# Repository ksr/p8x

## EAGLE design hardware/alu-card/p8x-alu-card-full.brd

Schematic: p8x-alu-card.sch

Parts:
CD1, CD2, CD3, CD4, CD5, CD6, CD7, CD8, CD9, CD10, CD11, CD12, CD13, CD14, CD15, CD16, CD17, CD18, CD19, CD20, CD21, CD22, CD23, CD24, CD25, CD26, CD27, CD28, CD29, CD30, CD31, CD32, CD33, CD34, CD35: 100nF; C_DISC1
J1: MABC96R
LED3, LED4: GRN; LED5
LED5: YEL; LED5
R4, R5: 1K; R_AXIAL
RP1: 1K; R_AXIAL
U1, U3, U5, U7: 74HCT377; DIP20
U2, U4, U6, U8, U16, U23: 74HCT244; DIP20
U9, U10: 74HCT181; DIP24W
U11: 74HCT182; DIP16
U12, U13, U14, U15, U22, U28, U29, U30, U32, U33: 74HCT157; DIP16
U17: FLAGS; DIP16
U18, U27: 74HCT260; DIP14
U19, U31, U35: 74HCT08; DIP14
U20, U21: 74HCT138; DIP16
U24: 74HCT32; DIP14
U25: 74HCT00; DIP14
U26: 74HCT74; DIP14
U34: 74HCT86; DIP14

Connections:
-CCLR: U26.1 (!1CLR), U31.8 (3Y)
-CLRCb: U25.11 (4Y), U31.10 (3B)
-DOEA: U2.1 (!G1), U2.19 (!G2), U20.14 (Y1)
-DOEALU: U16.1 (!G1), U16.19 (!G2), U19.9 (3A), U19.10 (3B), U20.10 (Y5)
-DOEB: U4.1 (!G1), U4.19 (!G2), U20.13 (Y2)
-DOEFLG: U20.9 (Y6), U23.1 (!G1)
-DOET: U6.1 (!G1), U6.19 (!G2), U20.12 (Y3)
-DOET2: U8.1 (!G1), U8.19 (!G2), U20.11 (Y4)
-LDA: U1.1 (!E), U21.14 (Y1)
-LDB: U3.1 (!E), U21.13 (Y2)
-LDT: U5.1 (!E), U21.12 (Y3)
-LDT2: U7.1 (!E), U21.11 (Y4)
-RES: J1.A11, U17.1 (!CLR), U31.9 (3A)
-SETCb: U25.3 (1Y), U26.4 (!1PRE)
ALUK: LED4.1 (K), U19.8 (3Y)
ALUM: J1.C23, U9.8 (M), U10.8 (M)
ALUS0: J1.C19, U9.6 (S0), U10.6 (S0)
ALUS1: J1.C20, U9.5 (S1), U10.5 (S1)
ALUS2: J1.C21, U9.4 (S2), U10.4 (S2), U34.9 (3A)
ALUS3: J1.C22, U9.3 (S3), U10.3 (S3)
AQ0: U1.2 (Q1), U2.2 (A1), U9.2 (A0)
AQ1: U1.5 (Q2), U2.4 (A2), U9.23 (A1)
AQ2: U1.6 (Q3), U2.6 (A3), U9.21 (A2)
AQ3: U1.9 (Q4), U2.8 (A4), U9.19 (A3)
AQ4: U1.12 (Q5), U2.11 (A5), U10.2 (A0)
AQ5: U1.15 (Q6), U2.13 (A6), U10.23 (A1)
AQ6: U1.16 (Q7), U2.15 (A7), U10.21 (A2)
AQ7: U1.19 (Q8), U2.17 (A8), U10.19 (A3), U34.1 (1A), U34.4 (2A)
BMX0: U9.1 (B0), U32.4 (Y1)
BMX1: U9.22 (B1), U32.7 (Y2)
BMX2: U9.20 (B2), U32.9 (Y3)
BMX3: U9.18 (B3), U32.12 (Y4)
BMX4: U10.1 (B0), U33.4 (Y1)
BMX5: U10.22 (B1), U33.7 (Y2)
BMX6: U10.20 (B2), U33.9 (Y3)
BMX7: U10.18 (B3), U33.12 (Y4), U34.5 (2B)
BQ0: U3.2 (Q1), U4.2 (A1), U32.2 (A1)
BQ1: U3.5 (Q2), U4.4 (A2), U32.5 (A2)
BQ2: U3.6 (Q3), U4.6 (A3), U32.11 (A3)
BQ3: U3.9 (Q4), U4.8 (A4), U32.14 (A4)
BQ4: U3.12 (Q5), U4.11 (A5), U33.2 (A1)
BQ5: U3.15 (Q6), U4.13 (A6), U33.5 (A2)
BQ6: U3.16 (Q7), U4.15 (A7), U33.11 (A3)
BQ7: U3.19 (Q8), U4.17 (A8), U33.14 (A4)
BSEL: J1.B28, U32.1 (S), U33.1 (S)
CFLG: U10.16 (CN4), U25.4 (2A), U25.5 (2B)
CFLGI: U25.6 (2Y), U29.2 (A1)
CG0: U9.17 (!G), U11.3 (!G0)
CG1: U10.17 (!G), U11.1 (!G1)
CIN: J1.C24, U9.7 (CN), U11.13 (CN), U30.2 (A1)
CLK: J1.A24, U1.11 (CLK), U3.11 (CLK), U5.11 (CLK), U7.11 (CLK), U31.1 (1A), U31.5 (2B)
CLKFC: U26.3 (1CLK), U31.3 (1Y)
CLKFZN: U17.9 (CLK), U31.6 (2Y)
CLRC: J1.B27, U25.12 (4A), U25.13 (4B)
CNX: U10.7 (CN), U11.12 (CNX)
CP0: U9.15 (!P), U11.4 (!P0)
CP1: U10.15 (!P), U11.2 (!P1)
D0: J1.A3, U1.3 (D1), U2.18 (Y1), U3.3 (D1), U4.18 (Y1), U5.3 (D1), U6.18 (Y1), U7.3 (D1), U8.18 (Y1), U16.18 (Y1), U23.18 (Y1), U27.1 (A1)
D1: J1.A4, U1.4 (D2), U2.16 (Y2), U3.4 (D2), U4.16 (Y2), U5.4 (D2), U6.16 (Y2), U7.4 (D2), U8.16 (Y2), U16.16 (Y2), U23.16 (Y2), U27.2 (B1)
D2: J1.A5, U1.7 (D3), U2.14 (Y3), U3.7 (D3), U4.14 (Y3), U5.7 (D3), U6.14 (Y3), U7.7 (D3), U8.14 (Y3), U16.14 (Y3), U23.14 (Y3), U27.11 (C1)
D3: J1.A6, U1.8 (D4), U2.12 (Y4), U3.8 (D4), U4.12 (Y4), U5.8 (D4), U6.12 (Y4), U7.8 (D4), U8.12 (Y4), U16.12 (Y4), U23.12 (Y4), U27.12 (D1)
D4: J1.A7, U1.13 (D5), U2.9 (Y5), U3.13 (D5), U4.9 (Y5), U5.13 (D5), U6.9 (Y5), U7.13 (D5), U8.9 (Y5), U16.9 (Y5), U27.13 (E1)
D5: J1.A8, U1.14 (D6), U2.7 (Y6), U3.14 (D6), U4.7 (Y6), U5.14 (D6), U6.7 (Y6), U7.14 (D6), U8.7 (Y6), U16.7 (Y6), U27.3 (A2)
D6: J1.A9, U1.17 (D7), U2.5 (Y7), U3.17 (D7), U4.5 (Y7), U5.17 (D7), U6.5 (Y7), U7.17 (D7), U8.5 (Y7), U16.5 (Y7), U27.4 (B2)
D7: J1.A10, U1.18 (D8), U2.3 (Y8), U3.18 (D8), U4.3 (Y8), U5.18 (D8), U6.3 (Y8), U7.18 (D8), U8.3 (Y8), U16.3 (Y8), U22.6 (B2), U27.5 (C2)
DLD0: J1.A16, U21.1 (A)
DLD1: J1.A17, U21.2 (B)
DLD2: J1.A18, U21.3 (C)
DLD3: J1.A19, U21.4 (!G2A)
DOE0: J1.A12, U20.1 (A)
DOE1: J1.A13, U20.2 (B)
DOE2: J1.A14, U20.3 (C)
DOE3: J1.A15, U20.4 (!G2A)
F0: U9.9 (F0), U12.2 (A1), U12.6 (B2), U28.2 (A1)
F1: U9.10 (F1), U12.5 (A2), U12.10 (B3)
F2: U9.11 (F2), U12.11 (A3), U12.13 (B4)
F3: U9.13 (F3), U12.14 (A4), U13.3 (B1)
F4: U10.9 (F0), U13.2 (A1), U13.6 (B2)
F5: U10.10 (F1), U13.5 (A2), U13.10 (B3)
F6: U10.11 (F2), U13.11 (A3), U13.13 (B4)
F7: U10.13 (F3), U13.14 (A4), U28.3 (B1), U34.2 (1B)
FC: J1.A27, U23.9 (Y5)
FENZN: U24.3 (1Y), U31.4 (2A)
FN: J1.A29, U23.5 (Y7)
FQC: U23.2 (A1), U23.11 (A5), U26.5 (1Q), U30.3 (B1)
FQN: U17.7 (Q2), U23.6 (A3), U23.15 (A7)
FQV: U17.10 (Q3), U23.8 (A4), U23.17 (A8)
FQZ: U17.2 (Q1), U23.4 (A2), U23.13 (A6)
FV: J1.A30, U23.3 (Y8)
FZ: J1.A28, U23.7 (Y6)
G0: U12.4 (Y1), U14.2 (A1)
G1: U12.7 (Y2), U14.3 (B1), U14.5 (A2)
G2: U12.9 (Y3), U14.6 (B2), U14.11 (A3)
G3: U12.12 (Y4), U14.10 (B3), U14.14 (A4)
G4: U13.4 (Y1), U14.13 (B4), U15.2 (A1)
G5: U13.7 (Y2), U15.3 (B1), U15.5 (A2)
G6: U13.9 (Y3), U15.6 (B2), U15.11 (A3)
G7: U13.12 (Y4), U15.10 (B3), U15.14 (A4)
GND: CD1.2, CD2.2, CD3.2, CD4.2, CD5.2, CD6.2, CD7.2, CD8.2, CD9.2, CD10.2, CD11.2, CD12.2, CD13.2, CD14.2, CD15.2, CD16.2, CD17.2, CD18.2, CD19.2, CD20.2, CD21.2, CD22.2, CD23.2, CD24.2, CD25.2, CD26.2, CD27.2, CD28.2, CD29.2, CD30.2, CD31.2, CD32.2, CD33.2, CD34.2, CD35.2, J1.A31, J1.A32, J1.B3, J1.B5, J1.B7, J1.B9, J1.B11, J1.B13, J1.B15, J1.B17, J1.B19, J1.B21, J1.B23, J1.B25, J1.B31, J1.B32, J1.C31, J1.C32, LED3.1 (K), U1.10 (GND), U2.10 (GND), U3.10 (GND), U4.10 (GND), U5.10 (GND), U6.10 (GND), U7.10 (GND), U8.10 (GND), U9.12 (GND), U10.12 (GND), U11.8 (GND), U12.8 (GND), U12.15 (!G), U13.8 (GND), U13.15 (!G), U14.8 (GND), U14.15 (!G), U15.8 (GND), U15.15 (!G), U16.10 (GND), U17.8 (GND), U18.7 (GND), U18.9 (D2), U18.10 (E2), U19.7 (GND), U19.12 (4A), U19.13 (4B), U20.5 (!G2B), U20.8 (GND), U21.5 (!G2B), U21.8 (GND), U22.8 (GND), U22.15 (!G), U23.10 (GND), U23.19 (!G2), U24.7 (GND), U24.9 (3A), U24.10 (3B), U24.12 (4A), U24.13 (4B), U25.7 (GND), U26.7 (GND), U26.11 (2CLK), U26.12 (2D), U27.7 (GND), U27.9 (D2), U27.10 (E2), U28.8 (GND), U28.15 (!G), U29.8 (GND), U29.15 (!G), U30.8 (GND), U30.15 (!G), U31.7 (GND)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
LDF: J1.A26, U24.1 (1A), U25.9 (3A), U25.10 (3B), U31.2 (1B)
LDFK: LED5.1 (K), U25.8 (3Y)
LDZN: J1.C28, U22.1 (S), U24.2 (1B)
LEDAL: LED4.2 (A), R4.2
LEDLF: LED5.2 (A), R5.2
LEDP: LED3.2 (A), RP1.2
NC: U26.2 (1D), U29.4 (Y1)
NS2: U34.8 (3Y), U34.13 (4B)
NSRC: U17.5 (D2), U22.7 (Y2)
R0: U14.4 (Y1), U16.2 (A1), U18.1 (A1)
R1: U14.7 (Y2), U16.4 (A2), U18.2 (B1)
R2: U14.9 (Y3), U16.6 (A3), U18.11 (C1)
R3: U14.12 (Y4), U16.8 (A4), U18.12 (D1)
R4: U15.4 (Y1), U16.11 (A5), U18.13 (E1)
R5: U15.7 (Y2), U16.13 (A6), U18.3 (A2)
R6: U15.9 (Y3), U16.15 (A7), U18.4 (B2)
R7: U15.12 (Y4), U16.17 (A8), U18.5 (C2), U22.5 (A2)
SETC: J1.C30, U25.1 (1A), U25.2 (1B)
SH0: J1.C25, U12.1 (S), U13.1 (S), U24.4 (2A), U28.1 (S)
SH1: J1.C26, U14.1 (S), U15.1 (S), U24.5 (2B)
SHANY: U24.6 (2Y), U29.1 (S)
SHCIN: J1.C29, U30.1 (S)
SHIN: U12.3 (B1), U15.13 (B4), U30.4 (Y1)
SHOUT: U28.4 (Y1), U29.3 (B1)
T2Q0: U7.2 (Q1), U8.2 (A1)
T2Q1: U7.5 (Q2), U8.4 (A2)
T2Q2: U7.6 (Q3), U8.6 (A3)
T2Q3: U7.9 (Q4), U8.8 (A4)
T2Q4: U7.12 (Q5), U8.11 (A5)
T2Q5: U7.15 (Q6), U8.13 (A6)
T2Q6: U7.16 (Q7), U8.15 (A7)
T2Q7: U7.19 (Q8), U8.17 (A8)
TQ0: U5.2 (Q1), U6.2 (A1), U32.3 (B1)
TQ1: U5.5 (Q2), U6.4 (A2), U32.6 (B2)
TQ2: U5.6 (Q3), U6.6 (A3), U32.10 (B3)
TQ3: U5.9 (Q4), U6.8 (A4), U32.13 (B4)
TQ4: U5.12 (Q5), U6.11 (A5), U33.3 (B1)
TQ5: U5.15 (Q6), U6.13 (A6), U33.6 (B2)
TQ6: U5.16 (Q7), U6.15 (A7), U33.10 (B3)
TQ7: U5.19 (Q8), U6.17 (A8), U33.13 (B4)
VCC: CD1.1, CD2.1, CD3.1, CD4.1, CD5.1, CD6.1, CD7.1, CD8.1, CD9.1, CD10.1, CD11.1, CD12.1, CD13.1, CD14.1, CD15.1, CD16.1, CD17.1, CD18.1, CD19.1, CD20.1, CD21.1, CD22.1, CD23.1, CD24.1, CD25.1, CD26.1, CD27.1, CD28.1, CD29.1, CD30.1, CD31.1, CD32.1, CD33.1, CD34.1, CD35.1, J1.A1, J1.A2, J1.B1, J1.B2, J1.C1, J1.C2, R4.1, R5.1, RP1.1, U1.20 (VCC), U2.20 (VCC), U3.20 (VCC), U4.20 (VCC), U5.20 (VCC), U6.20 (VCC), U7.20 (VCC), U8.20 (VCC), U9.24 (VCC), U10.24 (VCC), U11.5 (!G3), U11.6 (!P3), U11.14 (!P2), U11.15 (!G2), U11.16 (VCC), U12.16 (VCC), U13.16 (VCC), U14.16 (VCC), U15.16 (VCC), U16.20 (VCC), U17.16 (VCC), U18.14 (VCC), U19.14 (VCC), U20.6 (G1), U20.16 (VCC), U21.6 (G1), U21.16 (VCC), U22.16 (VCC), U23.20 (VCC), U24.14 (VCC), U25.14 (VCC), U26.10 (!2PRE), U26.13 (!2CLR), U26.14 (VCC), U27.14 (VCC), U28.16 (VCC), U29.16 (VCC), U30.16 (VCC), U31.14 (VCC), U32.16 (VCC), U33.16 (VCC), U34.10 (3B), U34.14 (VCC), U35.14 (VCC)
VSRC: U17.12 (D3), U35.3 (1Y)
VX1: U34.3 (1Y), U35.1 (1A)
VX2: U34.6 (2Y), U34.12 (4A)
VX4: U34.11 (4Y), U35.2 (1B)
ZBH: U19.5 (2B), U27.6 (Y2)
ZBL: U19.4 (2A), U27.8 (Y1)
ZBUS: U19.6 (2Y), U22.3 (B1)
ZFLG: U19.3 (1Y), U22.2 (A1)
ZH: U18.6 (Y2), U19.2 (1B)
ZL: U18.8 (Y1), U19.1 (1A)
ZSRC: U17.4 (D1), U22.4 (Y1)

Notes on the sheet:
P8X ALU CARD REV B (conventional carry, LDZN, SETC/CLRC, carry-coupled shifter)
CLK/FORCE GATES
74HCT08
V XOR
74HCT86
V AND
A REG
74HCT377
A OUT
74HCT244
B REG
B OUT
T REG
T OUT
T2 REG
T2 OUT
ALU LO
74HCT181
ALU HI
CLA
74HCT182
SH1 LO
74HCT157
SH1 HI
SH2 LO
SH2 HI
ALU OUT
Z DET
74HCT260
DOE DEC
74HCT138
DLD DEC
FLAG MUX
FLAG OUT
C FLAG FF
74HCT74
BUS Z-DET
SHIFT-OUT MUX
C-SRC MUX
SHIN MUX

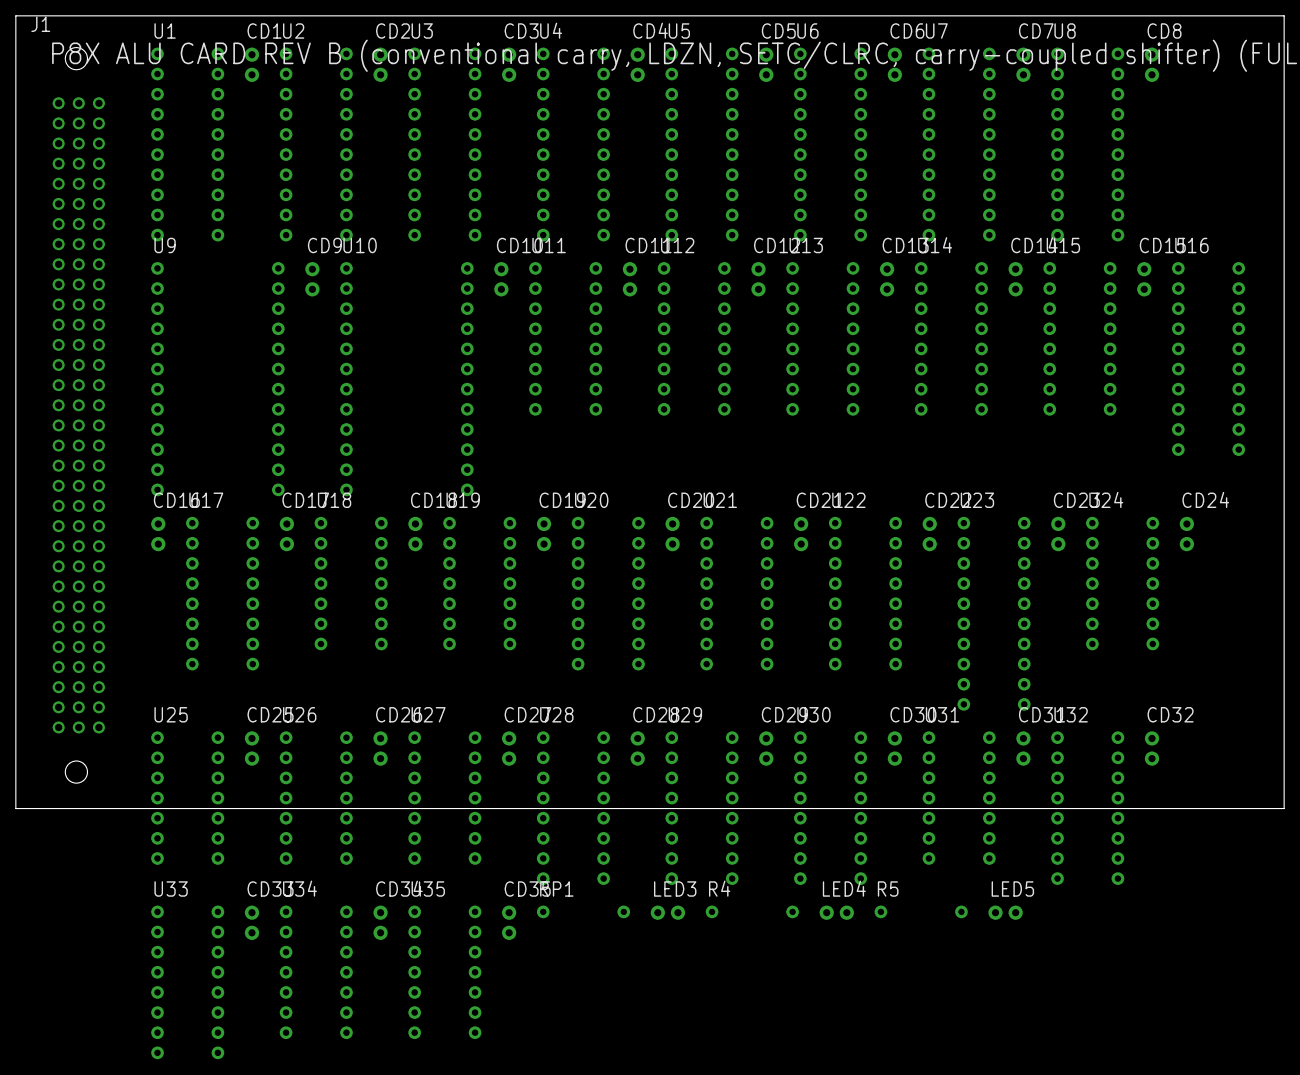
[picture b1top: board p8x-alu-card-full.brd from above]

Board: 4 copper layers, 160.0 x 100.0 mm, 77 parts (0 on the bottom side), 151 nets, no tracks yet.

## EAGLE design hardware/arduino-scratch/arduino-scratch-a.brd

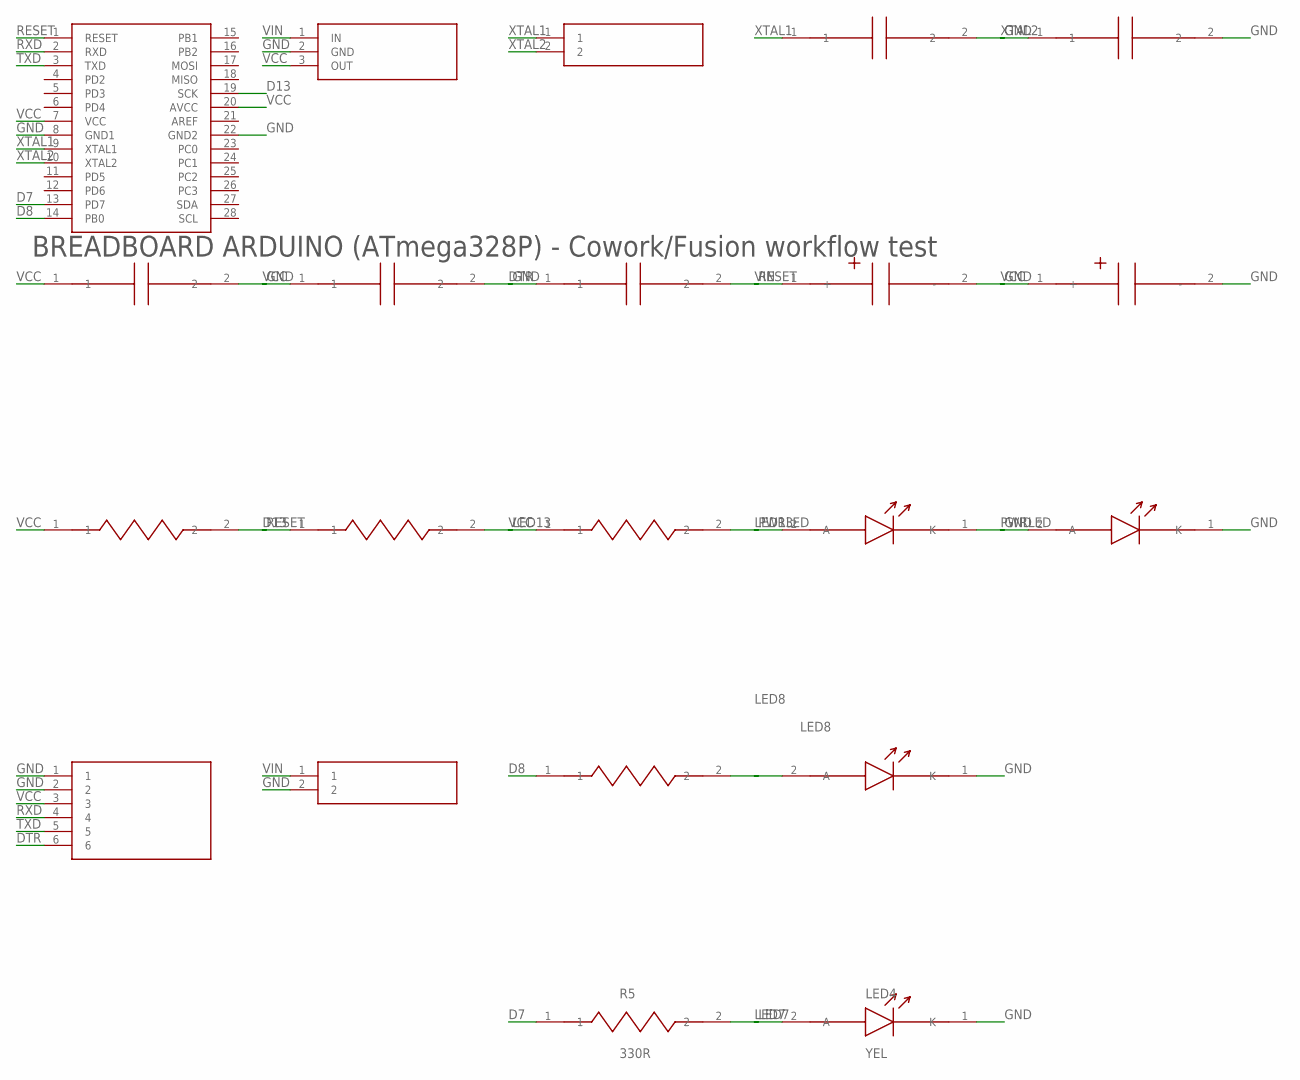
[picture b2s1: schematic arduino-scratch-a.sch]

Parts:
C1, C2: 22P; C_DISC
C3, C4, C5: 100N; C_DISC
C6, C7: 10U; CP_RADIAL
J1: FTDI; HDR6
J2: 7-12V DC; HDR2
LED1, LED3, LED4: YEL; LED5
LED2: GRN; LED5
R1: 10K; R_AXIAL
R2, R4, R5: 330R; R_AXIAL
R3: 1K; R_AXIAL
U1: ATMEGA328P-PU; DIP28N
U2: 7805; TO220
Y1: 16MHZ; HC49

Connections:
D7: R5.1, U1.13 (PD7)
D8: R4.1, U1.14 (PB0)
D13: R2.1, U1.19 (SCK)
DTR: C5.1, J1.6
GND: C1.2, C2.2, C3.2, C4.2, C6.2 (-), C7.2 (-), J1.1, J1.2, J2.2, LED1.1 (K), LED2.1 (K), LED3.1 (K), LED4.1 (K), U1.8 (GND1), U1.22 (GND2), U2.2 (GND)
LED7: LED4.2 (A), R5.2
LED8: LED3.2 (A), R4.2
LED13: LED1.2 (A), R2.2
PWRLED: LED2.2 (A), R3.2
RESET: C5.2, R1.2, U1.1 (RESET)
RXD: J1.4, U1.2 (RXD)
TXD: J1.5, U1.3 (TXD)
VCC: C3.1, C4.1, C7.1 (+), J1.3, R1.1, R3.1, U1.7 (VCC), U1.20 (AVCC), U2.3 (OUT)
VIN: C6.1 (+), J2.1, U2.1 (IN)
XTAL1: C1.1, U1.9 (XTAL1), Y1.1
XTAL2: C2.1, U1.10 (XTAL2), Y1.2

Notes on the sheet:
BREADBOARD ARDUINO (ATmega328P) - Cowork/Fusion workflow test

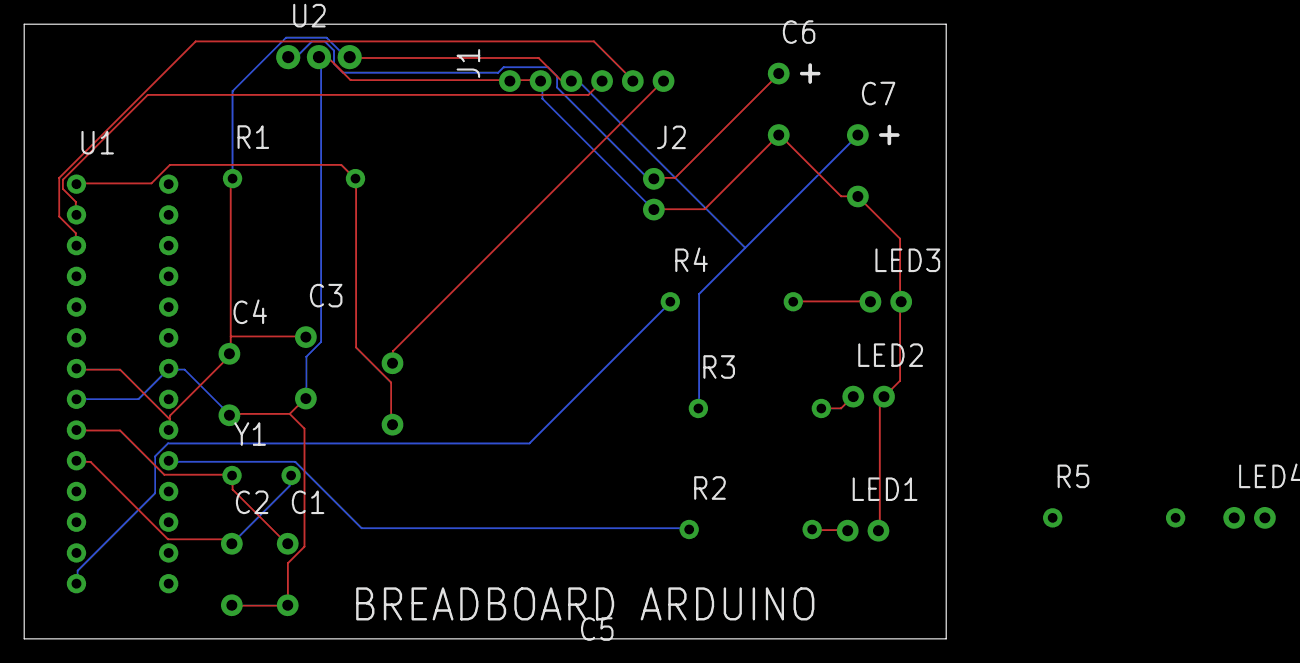
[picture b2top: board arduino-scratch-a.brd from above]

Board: 4 copper layers, 76.2 x 50.8 mm, 21 parts (0 on the bottom side), 16 nets.

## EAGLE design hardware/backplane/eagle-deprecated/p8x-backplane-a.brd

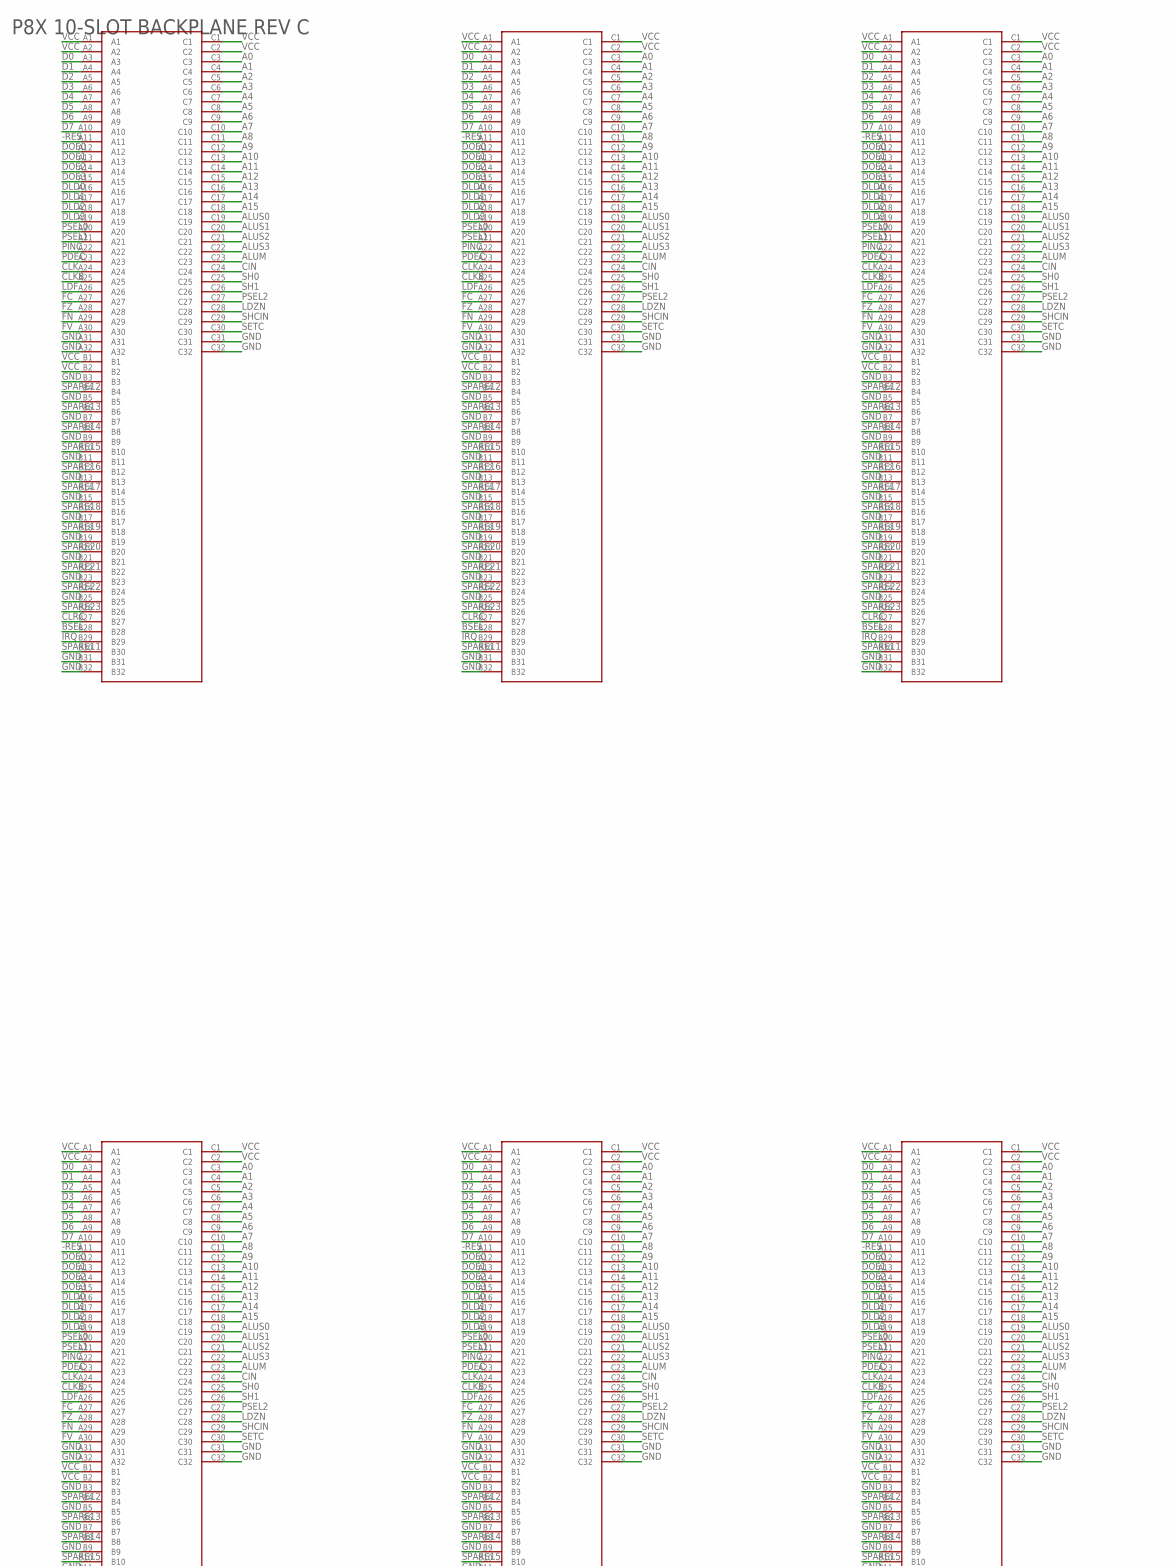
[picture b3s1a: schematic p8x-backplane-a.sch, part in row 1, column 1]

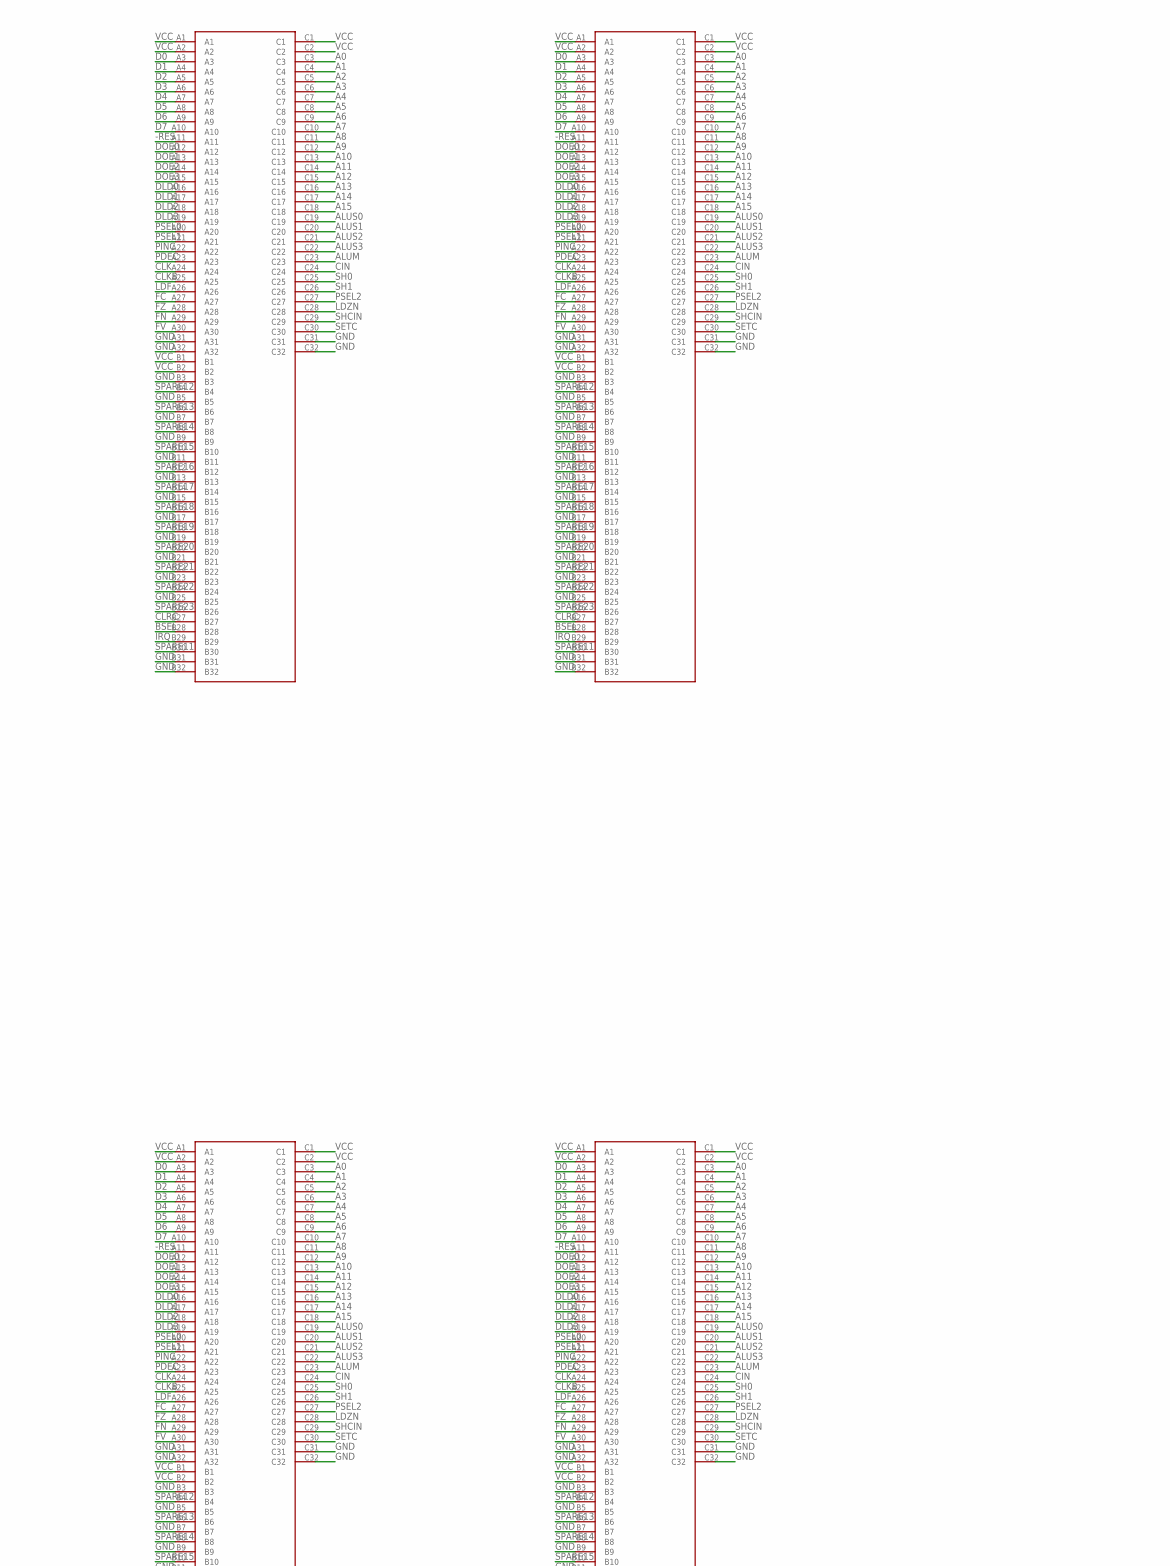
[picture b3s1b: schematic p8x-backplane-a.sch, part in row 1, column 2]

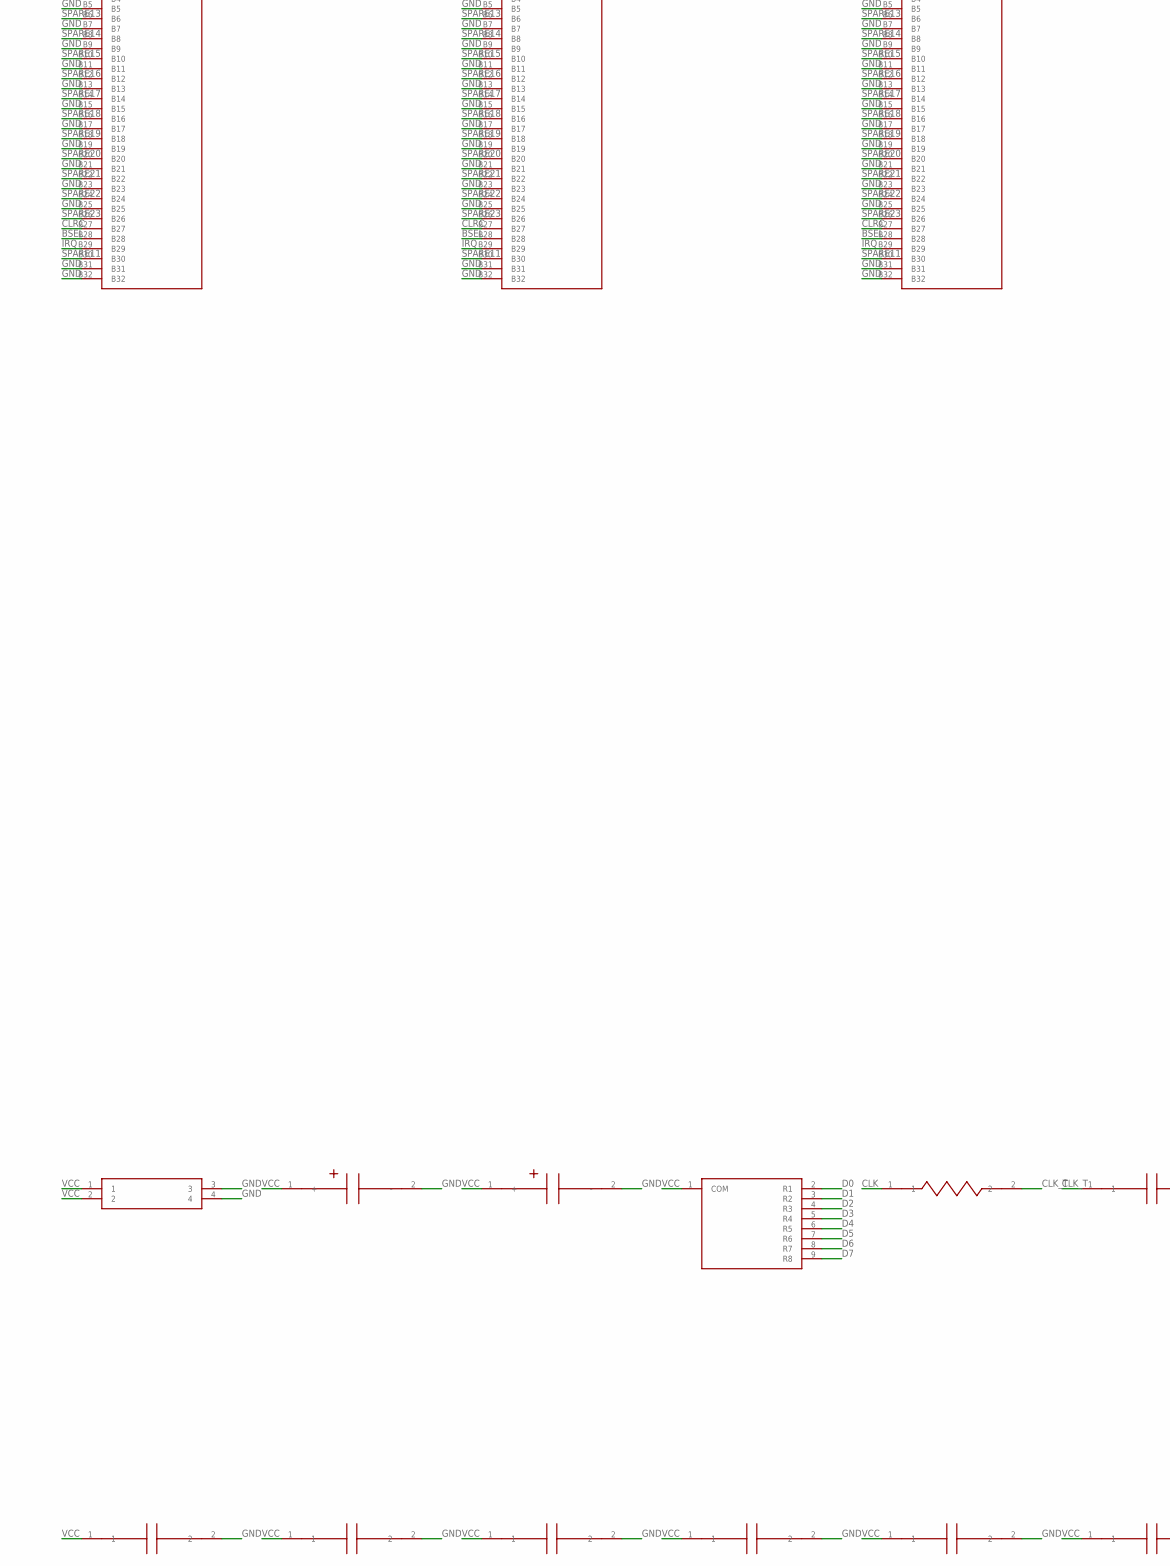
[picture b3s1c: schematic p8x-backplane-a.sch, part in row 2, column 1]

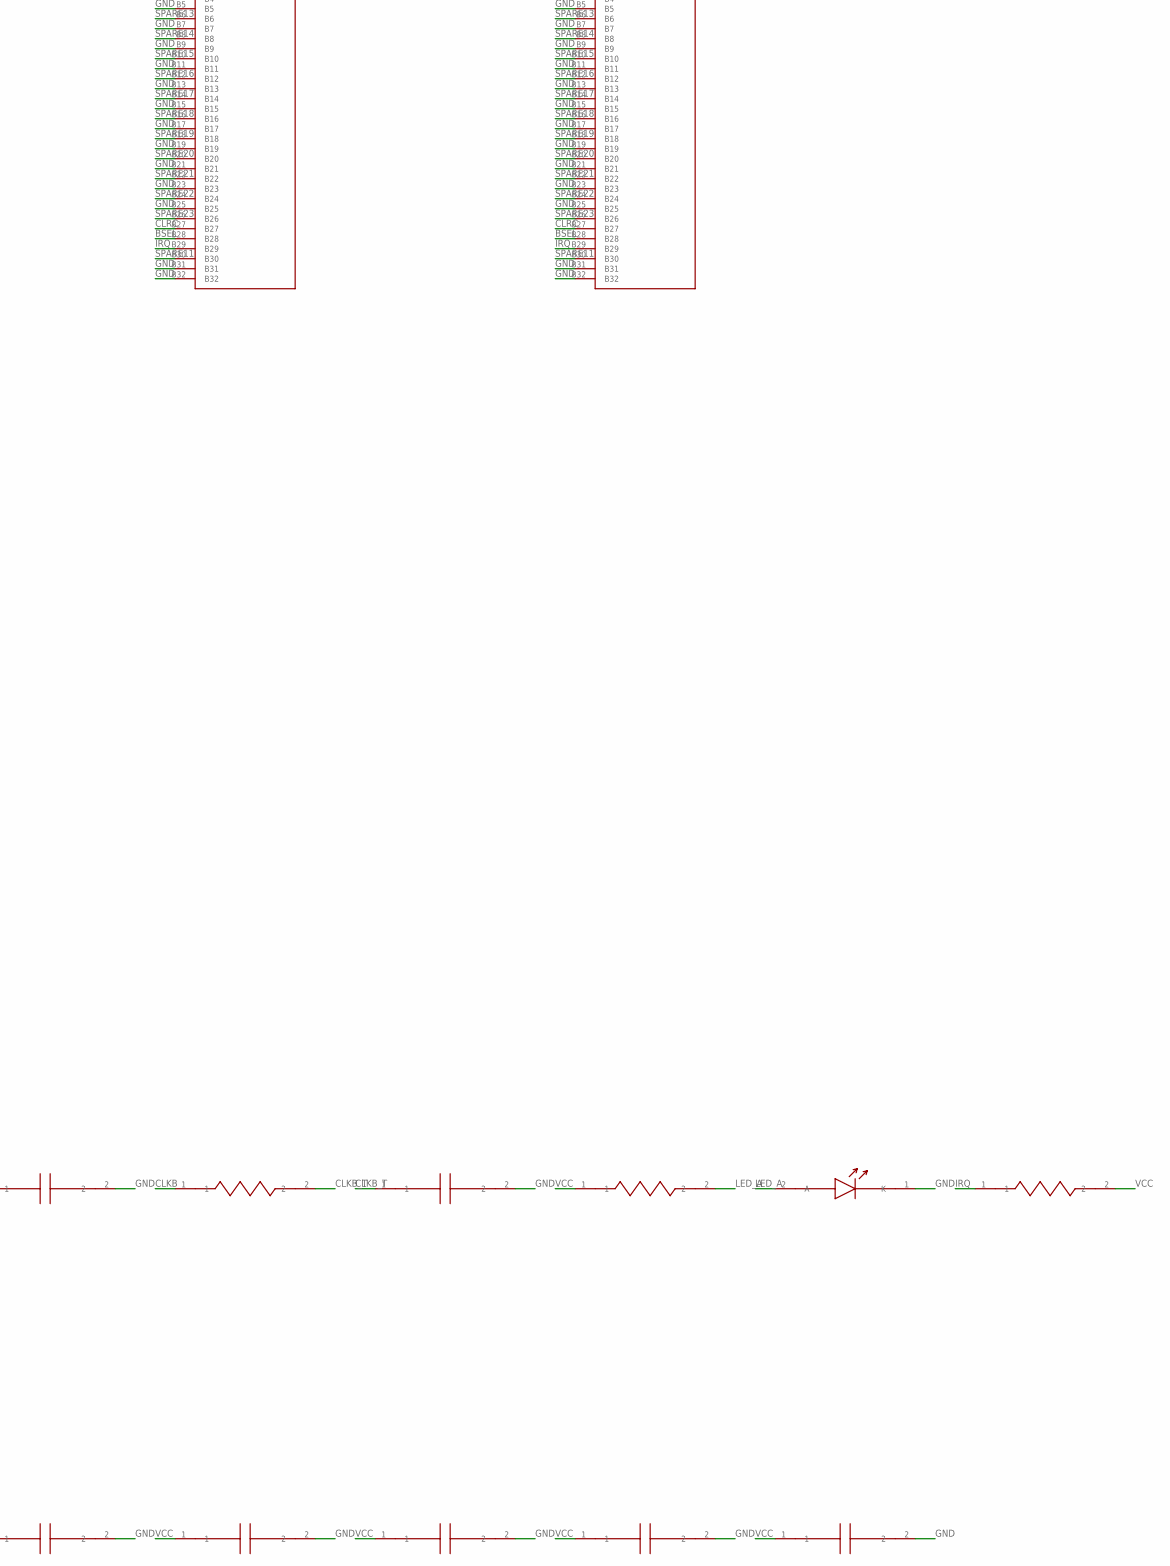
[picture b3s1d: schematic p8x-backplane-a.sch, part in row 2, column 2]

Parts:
C1, C2, C3, C4, C5, C6, C7, C8, C9, C10: 100nF; C_DISC1
C11, C12: 470uF; CP_RADIAL
C13, C14: 150pF; C_DISC
J1: SLOT1; FABC96S
J2: SLOT2; FABC96S
J3: SLOT3; FABC96S
J4: SLOT4; FABC96S
J5: SLOT5; FABC96S
J6: SLOT6; FABC96S
J7: SLOT7; FABC96S
J8: SLOT8; FABC96S
J9: SLOT9; FABC96S
J10: SLOT10; FABC96S
J11: PWR-5V; TB4
LED1: PWR; LED5
R1: 1K; R_AXIAL
R2, R3: 100R; R_AXIAL
R4: 10K; R_AXIAL
RN1: 8X10K; SIP9

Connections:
-RES: J1.A11, J2.A11, J3.A11, J4.A11, J5.A11, J6.A11, J7.A11, J8.A11, J9.A11, J10.A11
A0: J1.C3, J2.C3, J3.C3, J4.C3, J5.C3, J6.C3, J7.C3, J8.C3, J9.C3, J10.C3
A1: J1.C4, J2.C4, J3.C4, J4.C4, J5.C4, J6.C4, J7.C4, J8.C4, J9.C4, J10.C4
A2: J1.C5, J2.C5, J3.C5, J4.C5, J5.C5, J6.C5, J7.C5, J8.C5, J9.C5, J10.C5
A3: J1.C6, J2.C6, J3.C6, J4.C6, J5.C6, J6.C6, J7.C6, J8.C6, J9.C6, J10.C6
A4: J1.C7, J2.C7, J3.C7, J4.C7, J5.C7, J6.C7, J7.C7, J8.C7, J9.C7, J10.C7
A5: J1.C8, J2.C8, J3.C8, J4.C8, J5.C8, J6.C8, J7.C8, J8.C8, J9.C8, J10.C8
A6: J1.C9, J2.C9, J3.C9, J4.C9, J5.C9, J6.C9, J7.C9, J8.C9, J9.C9, J10.C9
A7: J1.C10, J2.C10, J3.C10, J4.C10, J5.C10, J6.C10, J7.C10, J8.C10, J9.C10, J10.C10
A8: J1.C11, J2.C11, J3.C11, J4.C11, J5.C11, J6.C11, J7.C11, J8.C11, J9.C11, J10.C11
A9: J1.C12, J2.C12, J3.C12, J4.C12, J5.C12, J6.C12, J7.C12, J8.C12, J9.C12, J10.C12
A10: J1.C13, J2.C13, J3.C13, J4.C13, J5.C13, J6.C13, J7.C13, J8.C13, J9.C13, J10.C13
A11: J1.C14, J2.C14, J3.C14, J4.C14, J5.C14, J6.C14, J7.C14, J8.C14, J9.C14, J10.C14
A12: J1.C15, J2.C15, J3.C15, J4.C15, J5.C15, J6.C15, J7.C15, J8.C15, J9.C15, J10.C15
A13: J1.C16, J2.C16, J3.C16, J4.C16, J5.C16, J6.C16, J7.C16, J8.C16, J9.C16, J10.C16
A14: J1.C17, J2.C17, J3.C17, J4.C17, J5.C17, J6.C17, J7.C17, J8.C17, J9.C17, J10.C17
A15: J1.C18, J2.C18, J3.C18, J4.C18, J5.C18, J6.C18, J7.C18, J8.C18, J9.C18, J10.C18
ALUM: J1.C23, J2.C23, J3.C23, J4.C23, J5.C23, J6.C23, J7.C23, J8.C23, J9.C23, J10.C23
ALUS0: J1.C19, J2.C19, J3.C19, J4.C19, J5.C19, J6.C19, J7.C19, J8.C19, J9.C19, J10.C19
ALUS1: J1.C20, J2.C20, J3.C20, J4.C20, J5.C20, J6.C20, J7.C20, J8.C20, J9.C20, J10.C20
ALUS2: J1.C21, J2.C21, J3.C21, J4.C21, J5.C21, J6.C21, J7.C21, J8.C21, J9.C21, J10.C21
ALUS3: J1.C22, J2.C22, J3.C22, J4.C22, J5.C22, J6.C22, J7.C22, J8.C22, J9.C22, J10.C22
BSEL: J1.B28, J2.B28, J3.B28, J4.B28, J5.B28, J6.B28, J7.B28, J8.B28, J9.B28, J10.B28
CIN: J1.C24, J2.C24, J3.C24, J4.C24, J5.C24, J6.C24, J7.C24, J8.C24, J9.C24, J10.C24
CLK: J1.A24, J2.A24, J3.A24, J4.A24, J5.A24, J6.A24, J7.A24, J8.A24, J9.A24, J10.A24, R2.1
CLKB: J1.A25, J2.A25, J3.A25, J4.A25, J5.A25, J6.A25, J7.A25, J8.A25, J9.A25, J10.A25, R3.1
CLKB_T: C14.1, R3.2
CLK_T: C13.1, R2.2
CLRC: J1.B27, J2.B27, J3.B27, J4.B27, J5.B27, J6.B27, J7.B27, J8.B27, J9.B27, J10.B27
D0: J1.A3, J2.A3, J3.A3, J4.A3, J5.A3, J6.A3, J7.A3, J8.A3, J9.A3, J10.A3, RN1.2 (R1)
D1: J1.A4, J2.A4, J3.A4, J4.A4, J5.A4, J6.A4, J7.A4, J8.A4, J9.A4, J10.A4, RN1.3 (R2)
D2: J1.A5, J2.A5, J3.A5, J4.A5, J5.A5, J6.A5, J7.A5, J8.A5, J9.A5, J10.A5, RN1.4 (R3)
D3: J1.A6, J2.A6, J3.A6, J4.A6, J5.A6, J6.A6, J7.A6, J8.A6, J9.A6, J10.A6, RN1.5 (R4)
D4: J1.A7, J2.A7, J3.A7, J4.A7, J5.A7, J6.A7, J7.A7, J8.A7, J9.A7, J10.A7, RN1.6 (R5)
D5: J1.A8, J2.A8, J3.A8, J4.A8, J5.A8, J6.A8, J7.A8, J8.A8, J9.A8, J10.A8, RN1.7 (R6)
D6: J1.A9, J2.A9, J3.A9, J4.A9, J5.A9, J6.A9, J7.A9, J8.A9, J9.A9, J10.A9, RN1.8 (R7)
D7: J1.A10, J2.A10, J3.A10, J4.A10, J5.A10, J6.A10, J7.A10, J8.A10, J9.A10, J10.A10, RN1.9 (R8)
DLD0: J1.A16, J2.A16, J3.A16, J4.A16, J5.A16, J6.A16, J7.A16, J8.A16, J9.A16, J10.A16
DLD1: J1.A17, J2.A17, J3.A17, J4.A17, J5.A17, J6.A17, J7.A17, J8.A17, J9.A17, J10.A17
DLD2: J1.A18, J2.A18, J3.A18, J4.A18, J5.A18, J6.A18, J7.A18, J8.A18, J9.A18, J10.A18
DLD3: J1.A19, J2.A19, J3.A19, J4.A19, J5.A19, J6.A19, J7.A19, J8.A19, J9.A19, J10.A19
DOE0: J1.A12, J2.A12, J3.A12, J4.A12, J5.A12, J6.A12, J7.A12, J8.A12, J9.A12, J10.A12
DOE1: J1.A13, J2.A13, J3.A13, J4.A13, J5.A13, J6.A13, J7.A13, J8.A13, J9.A13, J10.A13
DOE2: J1.A14, J2.A14, J3.A14, J4.A14, J5.A14, J6.A14, J7.A14, J8.A14, J9.A14, J10.A14
DOE3: J1.A15, J2.A15, J3.A15, J4.A15, J5.A15, J6.A15, J7.A15, J8.A15, J9.A15, J10.A15
FC: J1.A27, J2.A27, J3.A27, J4.A27, J5.A27, J6.A27, J7.A27, J8.A27, J9.A27, J10.A27
FN: J1.A29, J2.A29, J3.A29, J4.A29, J5.A29, J6.A29, J7.A29, J8.A29, J9.A29, J10.A29
FV: J1.A30, J2.A30, J3.A30, J4.A30, J5.A30, J6.A30, J7.A30, J8.A30, J9.A30, J10.A30
FZ: J1.A28, J2.A28, J3.A28, J4.A28, J5.A28, J6.A28, J7.A28, J8.A28, J9.A28, J10.A28
GND: C1.2, C2.2, C3.2, C4.2, C5.2, C6.2, C7.2, C8.2, C9.2, C10.2, C11.2 (-), C12.2 (-), C13.2, C14.2, J1.A31, J1.A32, J1.B3, J1.B5, J1.B7, J1.B9, J1.B11, J1.B13, J1.B15, J1.B17, J1.B19, J1.B21, J1.B23, J1.B25, J1.B31, J1.B32, J1.C31, J1.C32, J2.A31, J2.A32, J2.B3, J2.B5, J2.B7, J2.B9, J2.B11, J2.B13, J2.B15, J2.B17, J2.B19, J2.B21, J2.B23, J2.B25, J2.B31, J2.B32, J2.C31, J2.C32, J3.A31, J3.A32, J3.B3, J3.B5, J3.B7, J3.B9, J3.B11, J3.B13, J3.B15, J3.B17, J3.B19, J3.B21, J3.B23, J3.B25, J3.B31, J3.B32, J3.C31, J3.C32, J4.A31, J4.A32, J4.B3, J4.B5, J4.B7, J4.B9, J4.B11, J4.B13, J4.B15, J4.B17, J4.B19, J4.B21, J4.B23, J4.B25, J4.B31, J4.B32, J4.C31, J4.C32, J5.A31, J5.A32, J5.B3, J5.B5, J5.B7, J5.B9, J5.B11, J5.B13, J5.B15, J5.B17, J5.B19, J5.B21, J5.B23, J5.B25, J5.B31, J5.B32, J5.C31, J5.C32, J6.A31, J6.A32, J6.B3, J6.B5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
IRQ: J1.B29, J2.B29, J3.B29, J4.B29, J5.B29, J6.B29, J7.B29, J8.B29, J9.B29, J10.B29, R4.1
LDF: J1.A26, J2.A26, J3.A26, J4.A26, J5.A26, J6.A26, J7.A26, J8.A26, J9.A26, J10.A26
LDZN: J1.C28, J2.C28, J3.C28, J4.C28, J5.C28, J6.C28, J7.C28, J8.C28, J9.C28, J10.C28
LED_A: LED1.2 (A), R1.2
PDEC: J1.A23, J2.A23, J3.A23, J4.A23, J5.A23, J6.A23, J7.A23, J8.A23, J9.A23, J10.A23
PINC: J1.A22, J2.A22, J3.A22, J4.A22, J5.A22, J6.A22, J7.A22, J8.A22, J9.A22, J10.A22
PSEL0: J1.A20, J2.A20, J3.A20, J4.A20, J5.A20, J6.A20, J7.A20, J8.A20, J9.A20, J10.A20
PSEL1: J1.A21, J2.A21, J3.A21, J4.A21, J5.A21, J6.A21, J7.A21, J8.A21, J9.A21, J10.A21
PSEL2: J1.C27, J2.C27, J3.C27, J4.C27, J5.C27, J6.C27, J7.C27, J8.C27, J9.C27, J10.C27
SETC: J1.C30, J2.C30, J3.C30, J4.C30, J5.C30, J6.C30, J7.C30, J8.C30, J9.C30, J10.C30
SH0: J1.C25, J2.C25, J3.C25, J4.C25, J5.C25, J6.C25, J7.C25, J8.C25, J9.C25, J10.C25
SH1: J1.C26, J2.C26, J3.C26, J4.C26, J5.C26, J6.C26, J7.C26, J8.C26, J9.C26, J10.C26
SHCIN: J1.C29, J2.C29, J3.C29, J4.C29, J5.C29, J6.C29, J7.C29, J8.C29, J9.C29, J10.C29
SPARE11: J1.B30, J2.B30, J3.B30, J4.B30, J5.B30, J6.B30, J7.B30, J8.B30, J9.B30, J10.B30
SPARE12: J1.B4, J2.B4, J3.B4, J4.B4, J5.B4, J6.B4, J7.B4, J8.B4, J9.B4, J10.B4
SPARE13: J1.B6, J2.B6, J3.B6, J4.B6, J5.B6, J6.B6, J7.B6, J8.B6, J9.B6, J10.B6
SPARE14: J1.B8, J2.B8, J3.B8, J4.B8, J5.B8, J6.B8, J7.B8, J8.B8, J9.B8, J10.B8
SPARE15: J1.B10, J2.B10, J3.B10, J4.B10, J5.B10, J6.B10, J7.B10, J8.B10, J9.B10, J10.B10
SPARE16: J1.B12, J2.B12, J3.B12, J4.B12, J5.B12, J6.B12, J7.B12, J8.B12, J9.B12, J10.B12
SPARE17: J1.B14, J2.B14, J3.B14, J4.B14, J5.B14, J6.B14, J7.B14, J8.B14, J9.B14, J10.B14
SPARE18: J1.B16, J2.B16, J3.B16, J4.B16, J5.B16, J6.B16, J7.B16, J8.B16, J9.B16, J10.B16
SPARE19: J1.B18, J2.B18, J3.B18, J4.B18, J5.B18, J6.B18, J7.B18, J8.B18, J9.B18, J10.B18
SPARE20: J1.B20, J2.B20, J3.B20, J4.B20, J5.B20, J6.B20, J7.B20, J8.B20, J9.B20, J10.B20
SPARE21: J1.B22, J2.B22, J3.B22, J4.B22, J5.B22, J6.B22, J7.B22, J8.B22, J9.B22, J10.B22
SPARE22: J1.B24, J2.B24, J3.B24, J4.B24, J5.B24, J6.B24, J7.B24, J8.B24, J9.B24, J10.B24
SPARE23: J1.B26, J2.B26, J3.B26, J4.B26, J5.B26, J6.B26, J7.B26, J8.B26, J9.B26, J10.B26
VCC: C1.1, C2.1, C3.1, C4.1, C5.1, C6.1, C7.1, C8.1, C9.1, C10.1, C11.1 (+), C12.1 (+), J1.A1, J1.A2, J1.B1, J1.B2, J1.C1, J1.C2, J2.A1, J2.A2, J2.B1, J2.B2, J2.C1, J2.C2, J3.A1, J3.A2, J3.B1, J3.B2, J3.C1, J3.C2, J4.A1, J4.A2, J4.B1, J4.B2, J4.C1, J4.C2, J5.A1, J5.A2, J5.B1, J5.B2, J5.C1, J5.C2, J6.A1, J6.A2, J6.B1, J6.B2, J6.C1, J6.C2, J7.A1, J7.A2, J7.B1, J7.B2, J7.C1, J7.C2, J8.A1, J8.A2, J8.B1, J8.B2, J8.C1, J8.C2, J9.A1, J9.A2, J9.B1, J9.B2, J9.C1, J9.C2, J10.A1, J10.A2, J10.B1, J10.B2, J10.C1, J10.C2, J11.1, J11.2, R1.1, R4.2, RN1.1 (COM)

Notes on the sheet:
P8X 10-SLOT BACKPLANE REV C

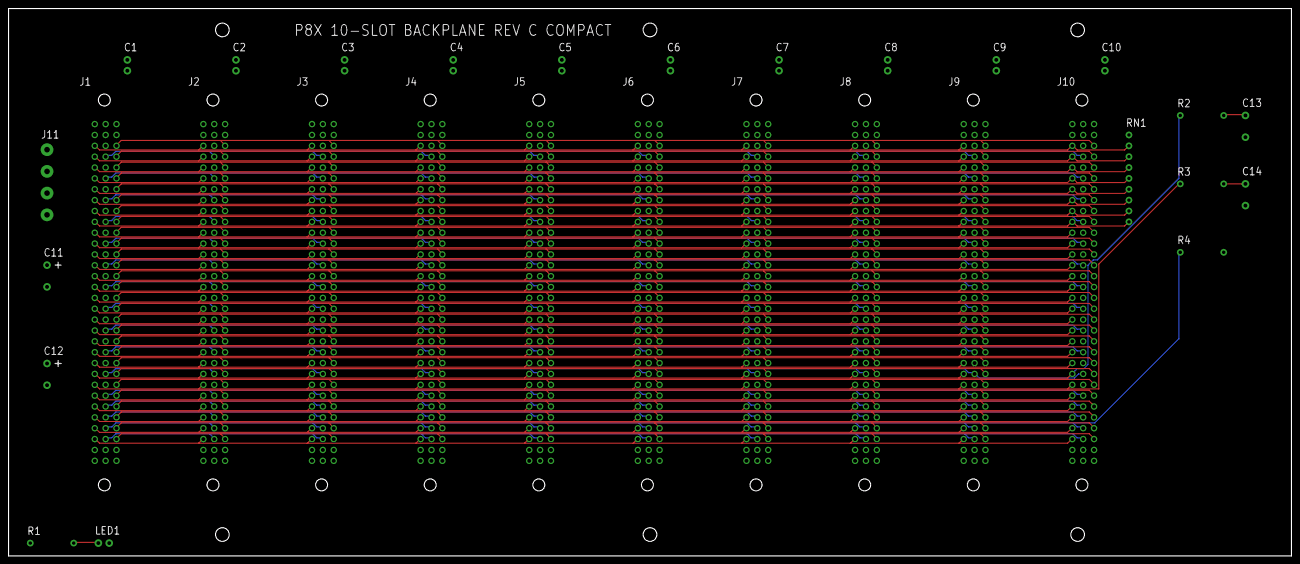
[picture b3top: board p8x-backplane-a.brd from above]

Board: 4 copper layers, 300.0 x 128.0 mm, 31 parts (0 on the bottom side), 77 nets.
